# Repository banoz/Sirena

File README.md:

# Sirena
Starbucks Sirena upgrade

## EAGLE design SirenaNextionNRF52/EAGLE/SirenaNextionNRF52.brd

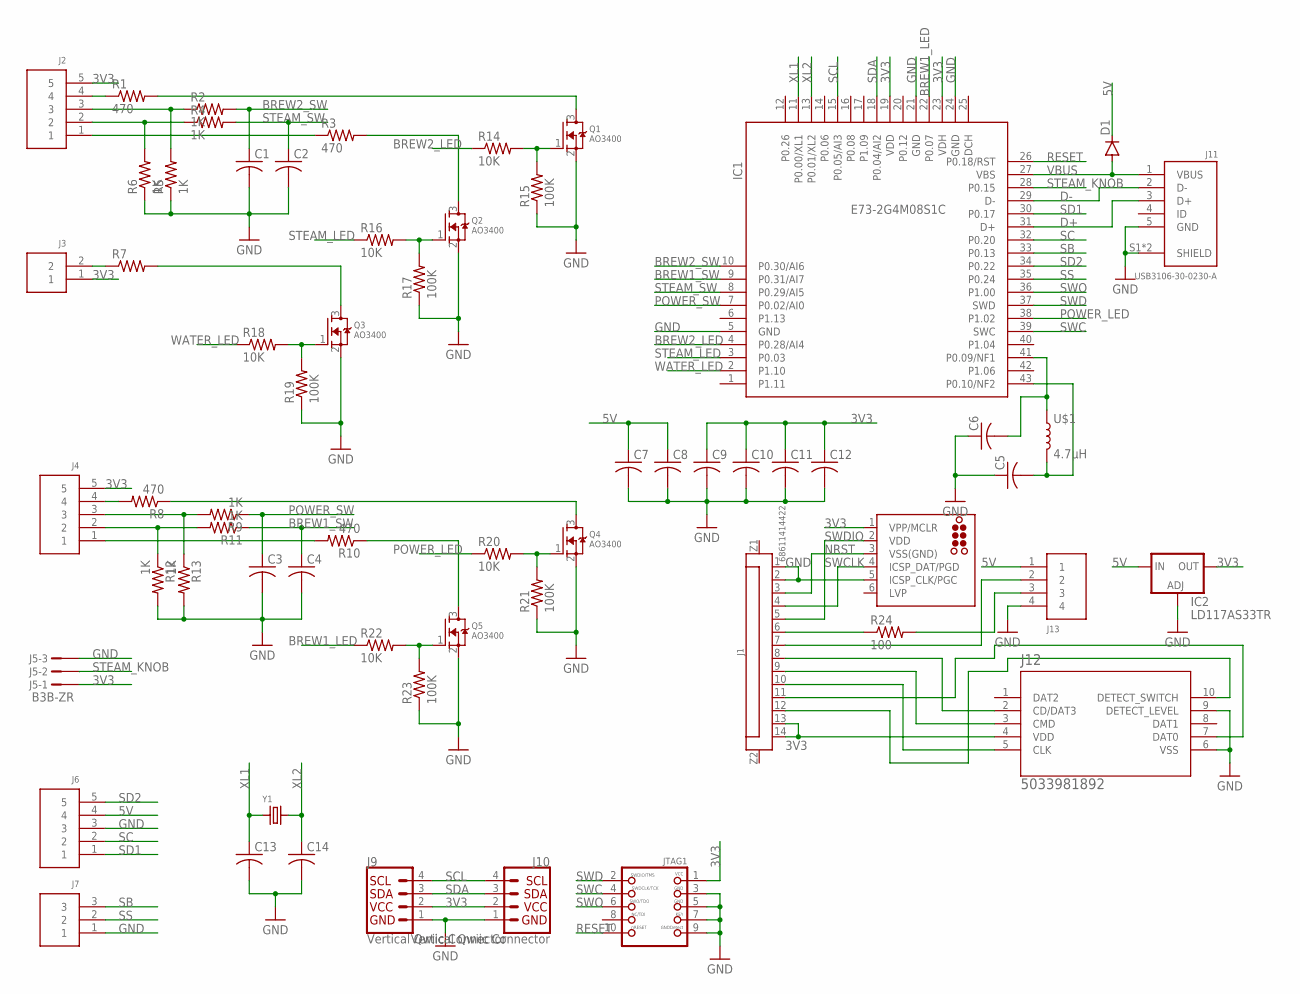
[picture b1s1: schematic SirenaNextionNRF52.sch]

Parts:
C1, C2, C3, C4, C5, C6, C7, C8, C9, C10, C11, C12, C13, C14: C-USC0603; C0603
D1: DIODE-SOD323-R; SOD323-R
IC1: E73-2G4M08S1C; SMD
IC2: LD117AS33TR; SOT223
J1: 68611414422
J2, J4, J6: 5PINB5B-PH-SM4-TB; B5B-PH-SM4-TB
J3: 2PINB2B-PH-SM4-TB; B2B-PH-SM4-TB
J5: B3B-ZR
J7: 3PINB3B-PH-SM4-TB; B3B-PH-SM4-TB
J9, J10: Vertical Qwiic Connector; JST04_1MM_VERT
J11: USB3106-30-0230-A
J12: 5033981892; 503398-1892_MOL
J13: 4PIN; B4B-XH-K-S
J14: TC2030-MCP-NL
JTAG1: JTAG-CORTEXM3; 2X05_1.27MM_SMT
Q1, Q2, Q3, Q4, Q5: AO3400; SOT23
R1, R3, R8, R10: 470; R0603
R2, R4, R5, R6, R9, R11, R12, R13: 1K; R0603
R7: R-US_R0603; R0603
R14, R16, R18, R20, R22: 10K; R0603
R15, R17, R19, R21, R23: 100K; R0603
R24: 100; R0603
U$1: 4.7μH; W3102
Y1: CRYSTAL8X3.8SMT; CRYSTAL_8X3.8

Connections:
3V3: C9.1, C10.1, C11.1, C12.1, IC1.19 (VDD), IC1.23 (VDH), IC2.4 (OUT), J1.13, J1.14, J2.5, J3.1, J4.5, J5.1, J9.2, J10.2, J12.4 (VDD), J14.1 (VPP/MCLR), JTAG1.1
5V: C7.1, C8.1, D1.C, IC2.3 (IN), J6.4, J13.1
BREW1_LED: IC1.22 (P0.07), R22.1
BREW1_SW: C4.1, IC1.9 (P0.31/AI7), R11.1
BREW2_LED: IC1.4 (P0.28/AI4), R14.1
BREW2_SW: C1.1, IC1.10 (P0.30/AI6), R2.2
D+: IC1.31 (D+), J11.3 (D+)
D-: IC1.29 (D-), J11.2 (D-)
GND: C1.2, C2.2, C3.2, C4.2, C5.1, C6.1, C7.2, C8.2, C9.2, C10.2, C11.2, C12.2, C13.2, C14.2, IC1.5 (GND), IC1.21 (GND), IC1.24 (GND), IC2.1 (ADJ), J1.1, J1.2, J5.3, J6.3, J7.1, J9.1, J10.1, J11.5 (GND), J11.S1 (SHIELD), J11.S2 (SHIELD), J12.6 (VSS), J12.9 (DETECT_LEVEL), J13.4, J14.5 (ICSP_CLK/PGC), JTAG1.3, JTAG1.5, JTAG1.7, JTAG1.9, Q1.2 (S), Q2.2 (S), Q3.2 (S), Q4.2 (S), Q5.2 (S), R5.1, R6.1, R12.2, R13.2, R15.1, R17.1, R19.1, R21.1, R23.1
unnamed: J3.2, R7.1
unnamed: Q2.3 (D), R3.2
unnamed: J2.4, R1.1
unnamed: J4.1, R10.2
unnamed: J2.3, R2.1, R5.2
unnamed: J2.2, R4.1, R6.2
unnamed: Q1.3 (D), R1.2
unnamed: J1.8, J12.2 (CD/DAT3)
unnamed: J1.6, R24.1
unnamed: C6.2, IC1.41 (P0.09/NF1), U$1.1
unnamed: Q2.1 (G), R16.2, R17.2
unnamed: Q1.1 (G), R14.2, R15.2
unnamed: C5.2, IC1.43 (P0.10/NF2), U$1.2
unnamed: Q3.3 (D), R7.2
unnamed: Q3.1 (G), R18.2, R19.2
unnamed: J4.4, R8.2
unnamed: J4.3, R9.2, R13.1
unnamed: J2.1, R3.1
unnamed: J4.2, R11.2, R12.1
unnamed: Q4.3 (D), R8.1
unnamed: Q5.3 (D), R10.1
unnamed: J13.3, R24.2
unnamed: J1.7, J13.2
unnamed: Q4.1 (G), R20.2, R21.2
unnamed: Q5.1 (G), R22.2, R23.2
unnamed: J1.9, J12.3 (CMD)
unnamed: J1.10, J12.5 (CLK)
unnamed: J1.11, J12.7 (DAT0)
unnamed: J1.12, J12.10 (DETECT_SWITCH)
NRST: J1.3, J14.3 (VSS(GND))
POWER_LED: IC1.38 (P1.02), R20.1
POWER_SW: C3.1, IC1.7 (P0.02/AI0), R9.1
RESET: IC1.26 (P0.18/RST), JTAG1.10
SB: IC1.33 (P0.13), J7.3
SC: IC1.32 (P0.20), J6.2
SCL: IC1.15 (P0.05/AI3), J9.4, J10.4
SD1: IC1.30 (P0.17), J6.1
SD2: IC1.34 (P0.22), J6.5
SDA: IC1.18 (P0.04/AI2), J9.3, J10.3
SS: IC1.35 (P0.24), J7.2
STEAM_KNOB: IC1.28 (P0.15), J5.2
STEAM_LED: IC1.3 (P0.03), R16.1
STEAM_SW: C2.1, IC1.8 (P0.29/AI5), R4.2
SWC: IC1.39 (SWC), JTAG1.4
SWCLK: J1.4, J14.4 (ICSP_DAT/PGD)
SWD: IC1.37 (SWD), JTAG1.2
SWDIO: J1.5, J14.2 (VDD)
SWO: IC1.36 (P1.00), JTAG1.6
VBUS: D1.A, IC1.27 (VBS), J11.1 (VBUS)
WATER_LED: IC1.2 (P1.10), R18.1
XL1: C13.1, IC1.11 (P0.00/XL1), Y1.P$1 (1)
XL2: C14.1, IC1.13 (P0.01/XL2), Y1.P$4 (2)

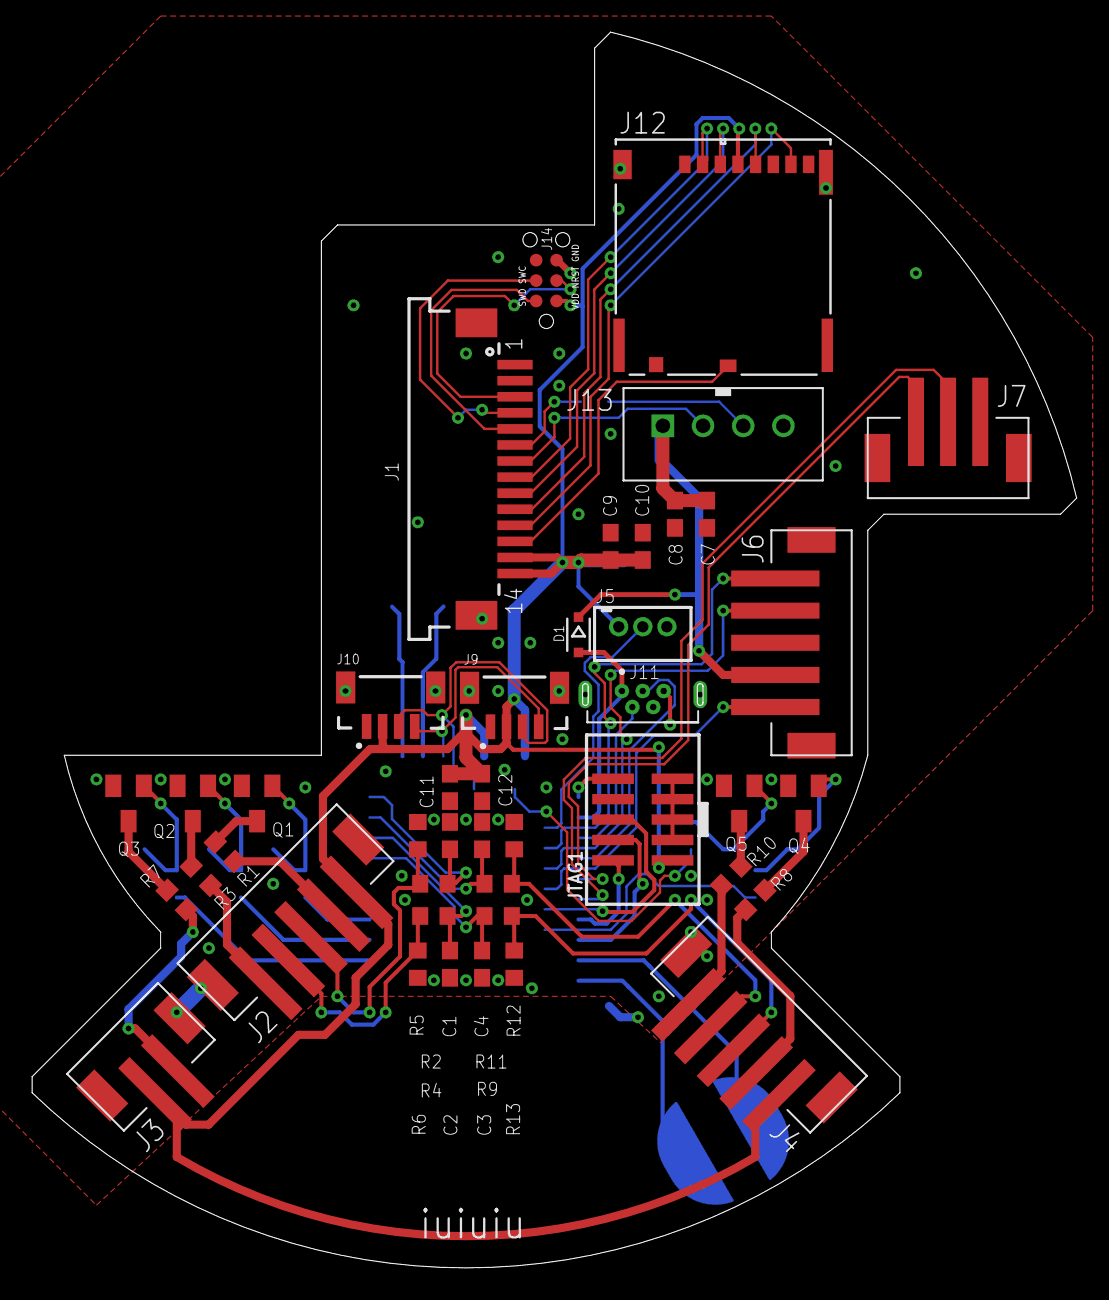
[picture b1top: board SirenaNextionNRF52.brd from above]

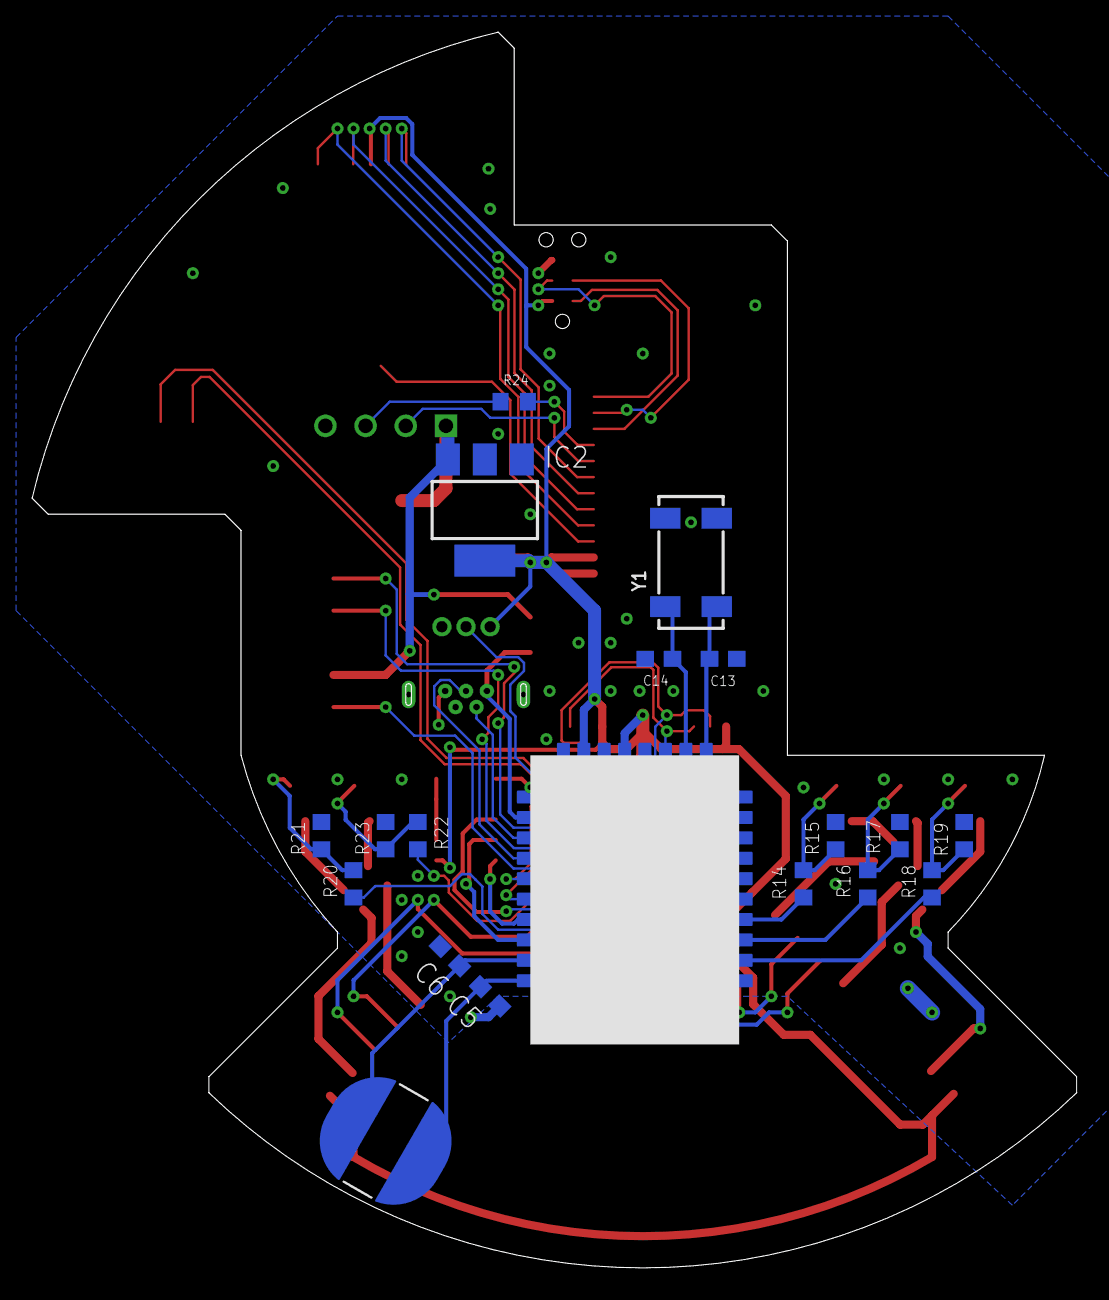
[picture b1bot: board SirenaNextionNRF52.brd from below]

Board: 2 copper layers, 65.0 x 76.9 mm, 62 parts (19 on the bottom side), 61 nets.

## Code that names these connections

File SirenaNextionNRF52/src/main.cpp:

#include <Arduino.h>
#include <bluefruit.h>
#include <nrfx_twis.h>

//#define SERIAL_DEBUG_ENABLED

#ifdef SERIAL_DEBUG_ENABLED
#define DEBUG_PRINT(x)     Serial.print (x)
#define DEBUG_PRINTF     Serial.printf
#define DEBUG_PRINTDEC(x)     Serial.print (x, DEC)
#define DEBUG_PRINTLN(x)  Serial.println (x)
#define DEBUG_PRINTLNF(x,y)  Serial.println (x,y)
#else
#define DEBUG_PRINT(x)
#define DEBUG_PRINTF(x,y)
#define DEBUG_PRINTDEC(x)
#define DEBUG_PRINTLN(x)
#define DEBUG_PRINTLNF(x,y)
#endif


#define CENTRAL_NAME "Sirena"
#define UUID16_SVC_SCALES 0xFFF0
#define UUID16_CHR_SCALES_READ 0x36F5
#define UUID16_CHR_SCALES_WRITE 0xFFF4

#define POWER_SW    18  // P0.02 (2)
#define BREW1_SW    21  // P0.31 (31)
#define BREW2_SW    16  // P0.30 (30)
#define STEAM_SW    20  // P0.29 (29)
#define STEAM_KNOB  24  // P0.15 (15)

#define POWER_LED   7   // P1.02 (34)
#define BREW1_LED   6   // P0.07 (7)
#define BREW2_LED   17  // P0.28 (28)
#define STEAM_LED   19  // P0.03 (3)
#define WATER_LED   4   // P1.10 (42)

#define SD1 29  // P0.17 (17)
#define SD2 30  // P0.22 (22)
#define SC  28  // P0.20 (20)
#define SB  25  // P0.13 (13) // SDA
#define SS  1   // P0.24 (24) // SCL

BLEClientService ss = BLEClientService(UUID16_SVC_SCALES);
BLEClientCharacteristic rc = BLEClientCharacteristic(UUID16_CHR_SCALES_READ);
BLEClientCharacteristic wc = BLEClientCharacteristic(UUID16_CHR_SCALES_WRITE);
BLEClientDis  clientDis;  // device information client
BLEClientBas  clientBas;  // battery client

const uint8_t tareRequest[7] = { 0x03, 0x0f, 0x00, 0x00, 0x00, 0x00, 0x0c };
volatile int16_t weight = 0;
volatile bool tareRequested = false;

volatile bool standardButtonsRequested = false;

bool powerLedState = false;
bool brew1LedState = false;
bool brew2LedState = false;
bool steamLedState = false;

bool powerState = false;
bool brew1State = false;
bool brew2State = false;
bool steamState = false;

void bleScanCallback(ble_gap_evt_adv_report_t* report) {
  Bluefruit.Central.connect(report);

  // For Softdevice v6: after received a report, scanner will be paused
  // We need to call Scanner resume() to continue scanning
  //Bluefruit.Scanner.resume();
}

void connectCallback(uint16_t conn_handle) {
  if (!ss.discover(conn_handle)) {
    Bluefruit.disconnect(conn_handle);
    return;
  }

  if (!rc.discover()) {
    Bluefruit.disconnect(conn_handle);
    return;
  }

  if (!wc.discover()) {
    Bluefruit.disconnect(conn_handle);
    return;
  }

  if (!wc.enableNotify()) {
    Bluefruit.disconnect(conn_handle);
    return;
  }
}

void disconnectCallback(uint16_t conn_handle, uint8_t reason) {
  (void)conn_handle;
  (void)reason;
  weight = 0;
}

void wcNotifyCallback(BLEClientCharacteristic* chr, uint8_t* data, uint16_t len) {
  if (len == 7) {
    if (data[0] == 0x03 && data[1] == 0xca) {
      weight = (data[2] << 8) | data[3];
      DEBUG_PRINT("weight ");
      DEBUG_PRINTLN(weight);
    }
  }
}

void bleSetup() {
  Bluefruit.begin(0, 1);
  Bluefruit.setTxPower(4);    // Check bluefruit.h for supported values
  Bluefruit.setName(CENTRAL_NAME);

  clientDis.begin();
  clientBas.begin();

  ss.begin();

  rc.begin();

  wc.setNotifyCallback(wcNotifyCallback);
  wc.begin();

  // Start Central Scan
  Bluefruit.setConnLedInterval(250);

  Bluefruit.Central.setDisconnectCallback(disconnectCallback);
  Bluefruit.Central.setConnectCallback(connectCallback);

  Bluefruit.Scanner.setRxCallback(bleScanCallback);
  Bluefruit.Scanner.restartOnDisconnect(true);
  Bluefruit.Scanner.setInterval(160, 80); // in unit of 0.625 ms
  Bluefruit.Scanner.filterUuid(ss.uuid);
  Bluefruit.Scanner.useActiveScan(false);
  Bluefruit.Scanner.start(0);
}

void parseLedState(uint8_t ledState) {
  brew1LedState = (ledState >> 0) & 1u;
  brew2LedState = (ledState >> 1) & 1u;
  steamLedState = (ledState >> 4) & 1u;
}

void parseLedStateEx(uint8_t ledState) {
  powerLedState = (ledState >> 2) & 1u;
}

const nrfx_twis_t twis = NRFX_TWIS_INSTANCE(0);

static uint8_t twisRxBuffer[4];
static uint8_t twisTxBuffer[4];

void wireReceiveEvent(uint32_t howMany) {
  DEBUG_PRINTF("wireReceiveEvent: %d\n\r", howMany);
  if (howMany == 1) { // register request
    if (twisRxBuffer[0] == 0x01u) {
      uint8_t statusByte = brew1State << 0 | brew2State << 1;
      statusByte ^= statusByte << 4;
      twisTxBuffer[0] = statusByte;
    }
    else if (twisRxBuffer[0] == 0x02u) {
      uint8_t statusByte = steamState << 0 | powerState << 2;
      statusByte ^= statusByte << 4;
      twisTxBuffer[0] = statusByte;
    }
  }
  else if (howMany == 2) {
    if (twisRxBuffer[0] == 0x00u) {
      parseLedState(twisRxBuffer[1]);
    }
    else if (twisRxBuffer[0] == 0x03u) { // scales comands
      if (twisRxBuffer[1] == 0xcau) {
        twisTxBuffer[0] = highByte(weight);
        twisTxBuffer[1] = lowByte(weight);
      }
      else if (twisRxBuffer[1] == 0x0fu) {
        tareRequested = true;
      }
    }
  }
  else if (howMany == 3) {
    if (twisRxBuffer[0] == 0x00u) {
      parseLedState(twisRxBuffer[1]);
      parseLedStateEx(twisRxBuffer[2]);
    }
  }
}

void twis_event_handler(nrfx_twis_evt_t const* const p_event) {
  DEBUG_PRINTF("twis_evt: %d\n\r", p_event->type);
  switch (p_event->type) {
  case NRFX_TWIS_EVT_READ_REQ:
    if (p_event->data.buf_req) {
      (void)nrfx_twis_tx_prepare(&twis, twisTxBuffer, sizeof(twisTxBuffer));
    }
    break;
  case NRFX_TWIS_EVT_READ_DONE:
    memset(twisTxBuffer, 0x00, sizeof(twisTxBuffer));
    break;
  case NRFX_TWIS_EVT_WRITE_REQ:
    if (p_event->data.buf_req) {
      (void)nrfx_twis_rx_prepare(&twis, twisRxBuffer, sizeof(twisRxBuffer));
    }
    break;
  case NRFX_TWIS_EVT_WRITE_DONE:
    wireReceiveEvent(p_event->data.rx_amount);
    break;
  default:
    break;
  }
}

void wireSetup() {
  nrfx_twis_config_t config = NRFX_TWIS_DEFAULT_CONFIG(24, 13, 0);

  if (NRFX_SUCCESS == nrfx_twis_init(&twis, &config, twis_event_handler)) {
    nrfx_twis_enable(&twis);
  }
}

void setup() {

#ifdef SERIAL_DEBUG_ENABLED
  Serial.begin(115200);
  while (!Serial) delay(10);   // for nrf52840 with native usb
  delay(5000);
  DEBUG_PRINTLN("starting...");
#endif

  pinMode(POWER_SW, INPUT);
  pinMode(BREW1_SW, INPUT);
  pinMode(BREW2_SW, INPUT);
  pinMode(STEAM_SW, INPUT);

  pinMode(POWER_LED, OUTPUT);
  pinMode(BREW1_LED, OUTPUT);
  pinMode(BREW2_LED, OUTPUT);
  pinMode(STEAM_LED, OUTPUT);
  pinMode(WATER_LED, OUTPUT);
  //pinMode(SB, OUTPUT);
  //pinMode(SS, OUTPUT);

  bleSetup();

  DEBUG_PRINTLN("bleSetup done");

  wireSetup();

  DEBUG_PRINTLN("wireSetup done");
}

void loop() {
  digitalWrite(POWER_LED, powerLedState ? HIGH : LOW);
  digitalWrite(BREW1_LED, brew1LedState ? HIGH : LOW);
  digitalWrite(BREW2_LED, brew2LedState ? HIGH : LOW);
  digitalWrite(STEAM_LED, steamLedState ? HIGH : LOW);

  powerState = digitalRead(POWER_SW);
  brew1State = digitalRead(BREW1_SW);
  brew2State = digitalRead(BREW2_SW);
  steamState = digitalRead(STEAM_SW);

  //digitalWrite(SB, brew1State ? LOW : HIGH);
  //digitalWrite(SS, steamState ? LOW : HIGH);

  if (tareRequested) {
    tareRequested = false;
    if (Bluefruit.Central.connected()) {
      rc.write(tareRequest, 7);
    }
  }
}

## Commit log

2022-11-05 hardware added
2023-04-01 SirenaNextionNRF52 EAGLE
2023-08-13 firmware
2023-08-14 pinMode fix
2023-08-17 steam led fix
2024-09-13 MaTouch ESP32-S3 Rotary IPS Display with Touch 2.1“ ST7701 adapter

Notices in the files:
parts and their libraries:
Wurth_Connectors_WR-FPC: Copyright: Würth Elektronik
microbuilder: This work is placed in the public domain, and may be freely used for commercial and non-commercial work with the following conditions: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
tag-connect: ©2009 ROFA.cz - modified and updated by Robert Darlington ‹rdarlington@gmail.com›
